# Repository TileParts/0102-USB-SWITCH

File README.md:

0102-USB-SWITCH
==========

一个 USB 转接器，附带自锁开关和 LED 指示灯，便于快速上下电而不需要重新插拔设备。

## 协议

[CERN-OHL-P-2.0](LICENSE)

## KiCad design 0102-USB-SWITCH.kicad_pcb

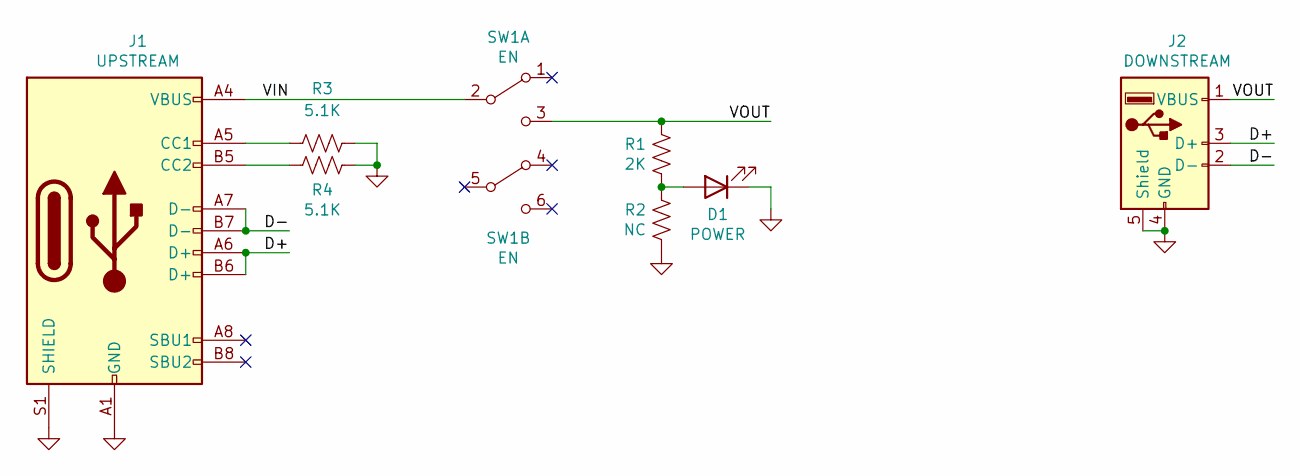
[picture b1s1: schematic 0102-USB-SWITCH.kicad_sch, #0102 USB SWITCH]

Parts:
D1: POWER; LED_0603_1608Metric; PartNumber C2286
J1: UPSTREAM; HRO_TYPE-C-31-M-12; PartNumber C165948
J2: DOWNSTREAM; MOLEX_48258-0001; PartNumber C505080
R1: 2K; R_0402_1005Metric; PartNumber C4109
R2: NC; R_0402_1005Metric
R3, R4: 5.1K; R_0402_1005Metric; PartNumber C25905
SW1: EN; SW_Push_DPDT_8.5x8.5mm; PartNumber C2911143

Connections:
/D+: J1.A6 (D+), J1.B6 (D+), J2.3 (D+)
/D-: J1.A7 (D-), J1.B7 (D-), J2.2 (D-)
/VIN: J1.A4 (VBUS), J1.A9 (VBUS), J1.B4 (VBUS), J1.B9 (VBUS), SW1.2 (B)
/VOUT: J2.1 (VBUS), R1.1, SW1.3 (C)
GND: D1.1 (K), J1.A1 (GND), J1.A12 (GND), J1.B1 (GND), J1.B12 (GND), J1.S1 (SHIELD), J2.4 (GND), J2.5 (Shield), R2.2, R3.1, R4.1
unnamed: D1.2 (A), R1.2, R2.1
unnamed: J1.A5 (CC1), R3.2
unnamed: J1.B5 (CC2), R4.2

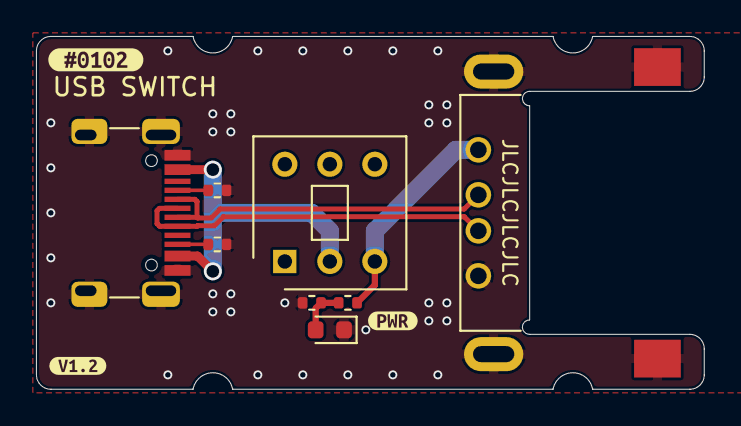
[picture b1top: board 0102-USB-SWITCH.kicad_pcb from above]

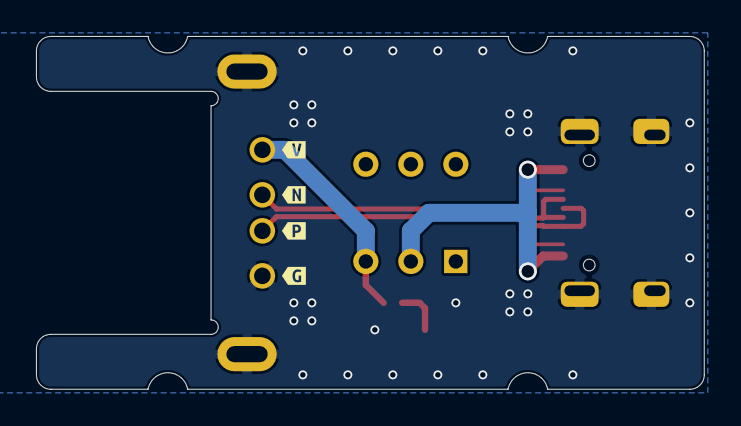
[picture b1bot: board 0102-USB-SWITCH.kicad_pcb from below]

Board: 2 copper layers, 37.1 x 19.6 mm, 15 parts (4 on the bottom side), 8 nets.

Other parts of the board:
kibuzzard-631FFD2B: G***; kibuzzard-631FFD2B
kibuzzard-631FFEA9: G***; kibuzzard-631FFEA9
kibuzzard-632D82D3: G***; kibuzzard-632D82D3
kibuzzard-632D82DD: G***; kibuzzard-632D82DD
kibuzzard-632D82E6: G***; kibuzzard-632D82E6
kibuzzard-632D82EF: G***; kibuzzard-632D82EF
kibuzzard-632D83AE: G***; kibuzzard-632D83AE

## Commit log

2022-09-13 Add BLOCK#0102 USB-C
2022-09-13 Rework USB-C for stand Type-A downstream
2022-09-13 Output gerber for USB-C V1.0
2022-09-13 Fix USB-C
2022-09-13 Migrate to KiCad 6
2022-09-13 Rework PCB for kibuzzard silk and laying USB-A slot
2022-09-13 Add README
2022-09-13 Output docs
2022-09-23 Rework with new design
2022-09-24 Output MF docs V1.2
